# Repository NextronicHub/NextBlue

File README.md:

# Nextronic NextBlue

With nextBlue, your Iot and Bluetooth applications are  easier to make
it's a 5v 16Mhz board based on the ATmega328P microcontroller with a built-in Bluetooth connector
NextBlue can be programmed over a USB Mini-B cable using the Arduino IDE: Just plug in the board, select “Arduino UNO” from the board menu and you’re ready to upload code.
NextBlue has all of the hardware peripherals like the Arduino.

## Features

  ATmega328 microcontroller with Optiboot (UNO) Bootloader<br />
  Input voltage - 7-15V<br />
  0-5V outputs<br />
  14 Digital I/O Pins (6 PWM outputs)<br />
  6 Analog Inputs<br />
  I2C, UART and SPI<br />
  32k Flash Memory<br />
  16MHz Clock Speed<br />
  All SMD Construction<br />
  R3 Shield Compatible<br />
  Bluetooth connector (EN, 5V, GND, TX, RX, STATE) <br />
  Software/hardware serial selector switch for the Bluetooth<br />

<br />
<br />
[FTDI driver](http://www.ftdichip.com/Drivers/VCP.htm)

Nextronic Product page:[NextBlue](http://nextronic.ma/product/nextblue/).

you can by it at: [makershop.ma](http://makershop.ma/).

## Repository Contents

/Hardware - Design files (.brd, .sch)  
/Firmware - bootloader  
/Documentation - datasheet and examples

## Product Versions

NextBlue_V1 first release

## License Information

The hardware is released under [Creative Commons ShareAlike 4.0 International](https://creativecommons.org/licenses/by-sa/4.0/).

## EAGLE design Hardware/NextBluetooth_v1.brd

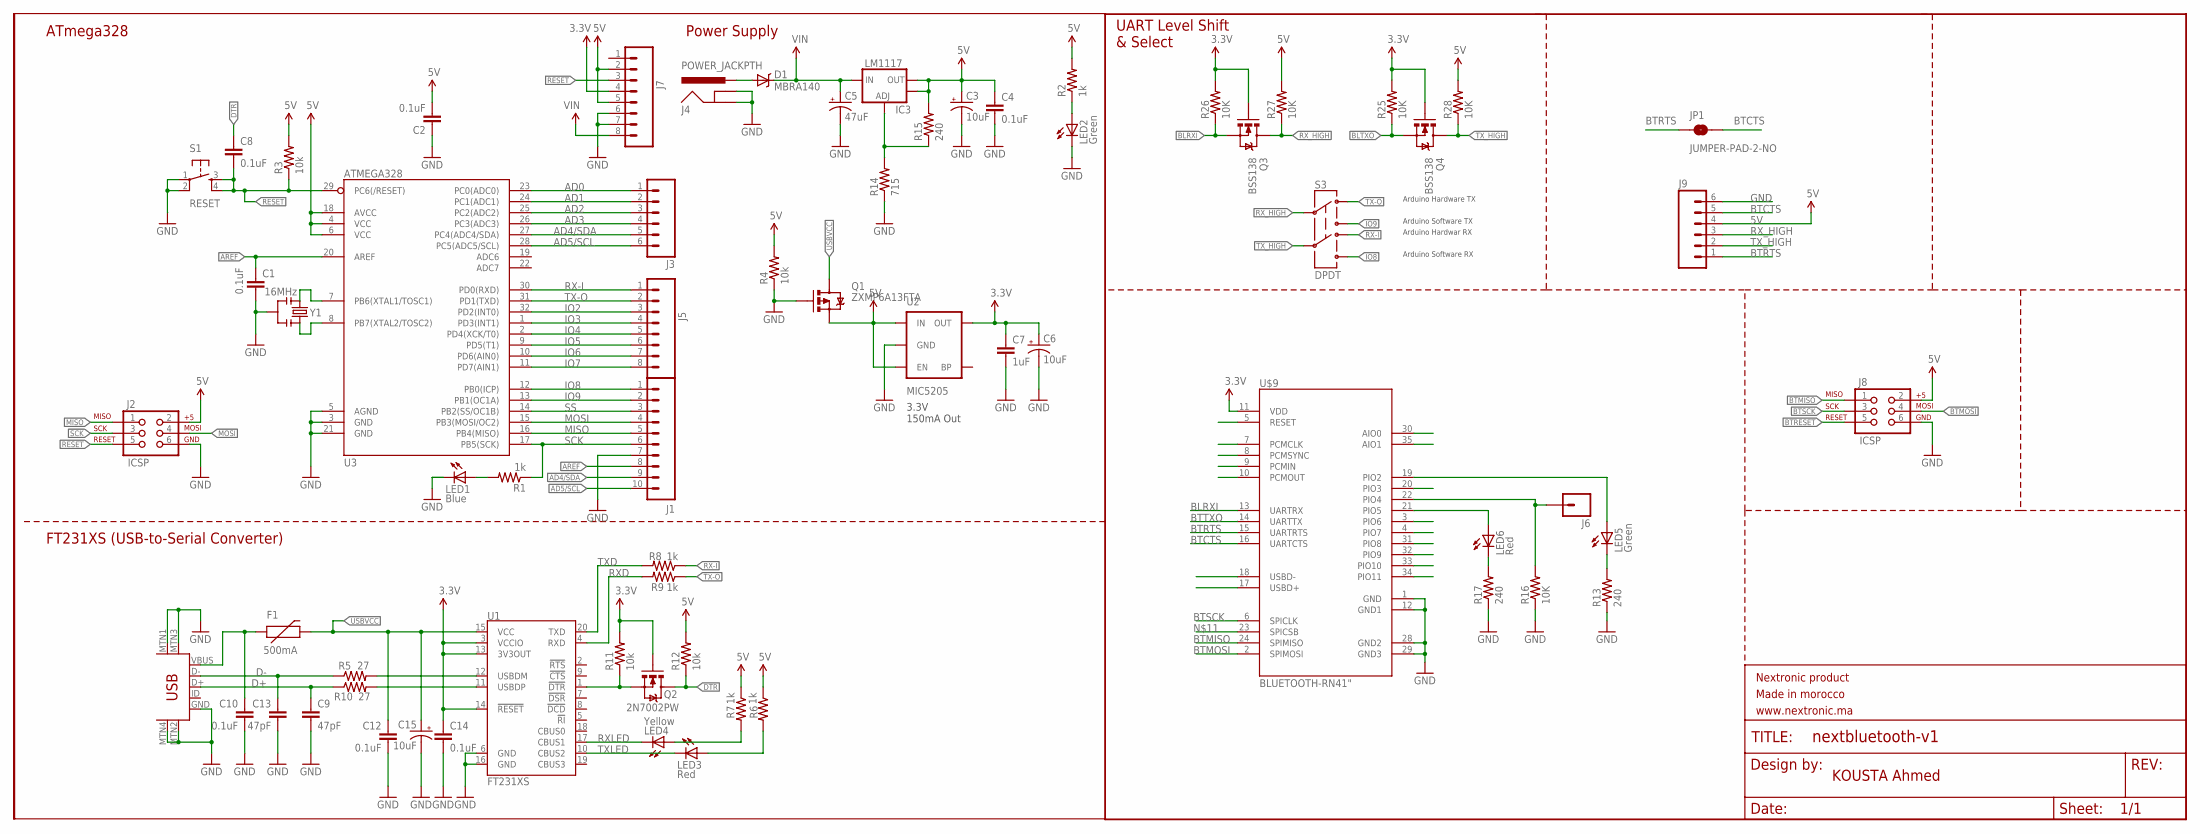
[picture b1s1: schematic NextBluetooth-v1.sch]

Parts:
C1, C2, C4, C8, C10, C12, C14: 0.1uF; 0603-CAP; MPN 0805B104K500CT
C3, C6, C15: 10uF; EIA3216; MPN MCSH21B104K101CT
C5: 47uF; PANASONIC_D; MPN EEEFT1H470AP
C7: 1uF; 0603-CAP; MPN ECA2GHG2R2
C9, C13: 47pF; 0603-CAP@1; MPN 08051A470JAT2A
D1: MBRA140; SMA-DIODE; MPN B140-13-F
F1: 500mA; PTC-1206; MPN 1N4148.
FRAME1: FRAME-LETTER; CREATIVE_COMMONS
IC3: LM1117; SOT223-ALT1; MPN LD1117S33TR
J1: M10SILK_FEMALE_PTH; 1X10
J2, J8: ICSP; 2X3
J3, J9: M06SILK_FEMALE_PTH; 1X06
J4: POWER_JACKPTH; POWER_JACK_PTH
J5, J7: M08; 1X08_ROUND
J6: M01NOSILK-KIT; 1X01NS-KIT
JP1: JUMPER-PAD-2-NO; PAD-JUMPER-2-NO_NO_SILK
LED1: Blue; LED-1206-NO_SILK; MPN 703-1028
LED2, LED5: Green; LED-1206-NO_SILK; MPN 703-1028
LED3, LED6: Red; LED-1206-NO_SILK; MPN 703-1028
LED4: Yellow; LED-1206-NO_SILK; MPN TLUY2401
Q1: ZXMP6A13FTA; SOT23-3; MPN ZXMP6A13FTA
Q2: 2N7002PW; SOT323; MPN 2N7002PW
Q3, Q4: BSS138; SOT23-3; MPN BSS138PW
R1, R2, R6, R7, R8, R9: 1k; 0603-RES; MPN ERA6AEB102V
R3, R4, R11, R12: 10k; 0603-RES; MPN MC0063W0603510K
R5, R10: 27; 0603-RES; MPN 22-27-2021
R13, R15, R17: 240; 0603-RES; MPN MCMR06X2200FTL
R14: 715; 0603-RES; MPN RC0603JR-07150RL
R16: 10K; 0603-RES; MPN RR0816P-103-B-T5
R25, R26, R27, R28: 10K; 0603-RES@2; MPN RR0816P-103-B-T5
S1: RESET; TACTILE_SWITCH_SMD
S3: DPDT; AYZ0202
U1: FT231XS; SSOP20_L; MPN FT231XS
U2: MIC5205; SOT23-5; MPN MIC5205-5.0YM5 TR
U3: ATMEGA328; TQFP32-08; MPN ATMEGA328P-AN
U$9: BLUETOOTH-RN41"; RN41
U$13: USB-MINIB-5PIN; USB-MINIB
Y1: 16MHz; RESONATOR-SMD

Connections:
3.3V: C6.A (+), C7.1, C14.1, J7.4, Q2.1 (G), Q3.1 (G), Q4.1 (G), R11.2, R25.2, R26.2, U1.3 (VCCIO), U1.13 (3V3OUT), U1.14 (!RESET), U2.5 (OUT), U$9.11 (VDD)
5V: C2.2, C3.A (+), C4.1, IC3.2 (OUT), IC3.4 (OUT), J2.2, J7.2, J7.5, J8.2, J9.4, Q1.2 (S), R2.2, R3.2, R4.2, R6.1, R7.1, R12.2, R15.2, R27.2, R28.2, U2.1 (IN), U2.3 (EN), U3.4 (VCC), U3.6 (VCC), U3.18 (AVCC)
AD0: J3.1, U3.23 (PC0(ADC0))
AD1: J3.2, U3.24 (PC1(ADC1))
AD2: J3.3, U3.25 (PC2(ADC2))
AD3: J3.4, U3.26 (PC3(ADC3))
AD4/SDA: J1.9, J3.5, U3.27 (PC4(ADC4/SDA))
AD5/SCL: J1.10, J3.6, U3.28 (PC5(ADC5/SCL))
AREF: C1.1, J1.8, U3.20 (AREF)
BLRXI: Q3.2 (S), R26.1, U$9.13 (UARTRX)
BLTXO: Q4.2 (S), R25.1
BTCTS: J9.5, JP1.2, U$9.16 (UARTCTS)
BTMISO: J8.1, U$9.24 (SPIMISO)
BTMOSI: J8.4, U$9.2 (SPIMOSI)
BTRESET: J8.5, U$9.5 (RESET)
BTRTS: J9.1, JP1.1, U$9.15 (UARTRTS)
BTSCK: J8.3, U$9.6 (SPICLK)
BTTXO: U$9.14 (UARTTX)
D+: C9.1, R10.1, U$13.D+
D-: C13.1, R5.1, U$13.D-
DTR: C8.1, Q2.3 (D), R12.1
GND: C1.2, C2.1, C3.C (-), C4.2, C5.-, C6.C (-), C7.2, C9.2, C10.2, C12.2, C13.2, C14.2, C15.C (-), J1.7, J2.6, J4.GND, J4.GNDBREAK, J7.6, J7.7, J8.6, J9.6, LED1.C, LED2.C, Q1.1 (G), R4.1, R13.1, R14.1, R16.1, R17.1, S1.1, S1.2, U1.6 (GND), U1.16 (GND), U2.2 (GND), U3.3 (GND), U3.5 (AGND), U3.21 (GND), U$9.1 (GND), U$9.12 (GND1), U$9.28 (GND2), U$9.29 (GND3), U$13.GND, U$13.MTN1 (MTN2), U$13.MTN2 (MTN3), U$13.MTN3 (MTN1), U$13.MTN4, Y1.2
IO2: J5.3, U3.32 (PD2(INT0))
IO3: J5.4, U3.1 (PD3(INT1))
IO4: J5.5, U3.2 (PD4(XCK/T0))
IO5: J5.6, U3.9 (PD5(T1))
IO6: J5.7, U3.10 (PD6(AIN0))
IO7: J5.8, U3.11 (PD7(AIN1))
IO8: J1.1, S3.6, U3.12 (PB0(ICP))
IO9: J1.2, S3.3, U3.13 (PB1(OC1A))
MISO: J1.5, J2.1, U3.16 (PB4(MISO))
MOSI: J1.4, J2.4, U3.15 (PB3(MOSI/OC2))
unnamed: LED1.A, R1.2
unnamed: LED2.A, R2.1
unnamed: U3.7 (PB6(XTAL1/TOSC1)), Y1.1
unnamed: U3.8 (PB7(XTAL2/TOSC2)), Y1.3
unnamed: D1.A, J4.PWR
unnamed: R5.2, U1.12 (USBDM)
unnamed: R10.2, U1.11 (USBDP)
unnamed: LED3.A, R6.2
unnamed: LED4.A, R7.2
unnamed: Q2.2 (S), R11.1, U1.1 (!DTR)
unnamed: IC3.1 (ADJ), R14.2, R15.1
unnamed: LED6.A, U$9.21 (PIO5)
unnamed: J6.1, R16.2, U$9.22 (PIO4)
unnamed: LED5.A, U$9.19 (PIO2)
unnamed: LED5.C, R13.2
unnamed: LED6.C, R17.2
RESET: C8.2, J2.5, J7.3, R3.1, S1.3, S1.4, U3.29 (PC6(/RESET))
RX-I: J5.1, R8.1, S3.4, U3.30 (PD0(RXD))
RXD: R9.2, U1.4 (RXD)
RXLED: LED4.C, U1.17 (CBUS1)
RX_HIGH: J9.3, Q3.3 (D), R27.1, S3.2
SCK: J1.6, J2.3, R1.1, U3.17 (PB5(SCK))
SS: J1.3, U3.14 (PB2(SS/OC1B))
TX-O: J5.2, R9.1, S3.1, U3.31 (PD1(TXD))
TXD: R8.2, U1.20 (TXD)
TXLED: LED3.C, U1.10 (CBUS2)
TX_HIGH: J9.2, Q4.3 (D), R28.1, S3.5
USBVCC: C12.1, C15.A (+), F1.2, Q1.3 (D), U1.15 (VCC)
VIN: C5.+, D1.C, IC3.3 (IN), J7.8
VUSB: C10.1, F1.1, U$13.VBUS

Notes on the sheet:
Power Supply
ATmega328
FT231XS (USB-to-Serial Converter)
3.3V 150mA Out
KOUSTA Ahmed
UART Level Shift & Select
Arduino Software TX
Arduino Software RX
Arduino Hardwar RX
Arduino Hardware TX

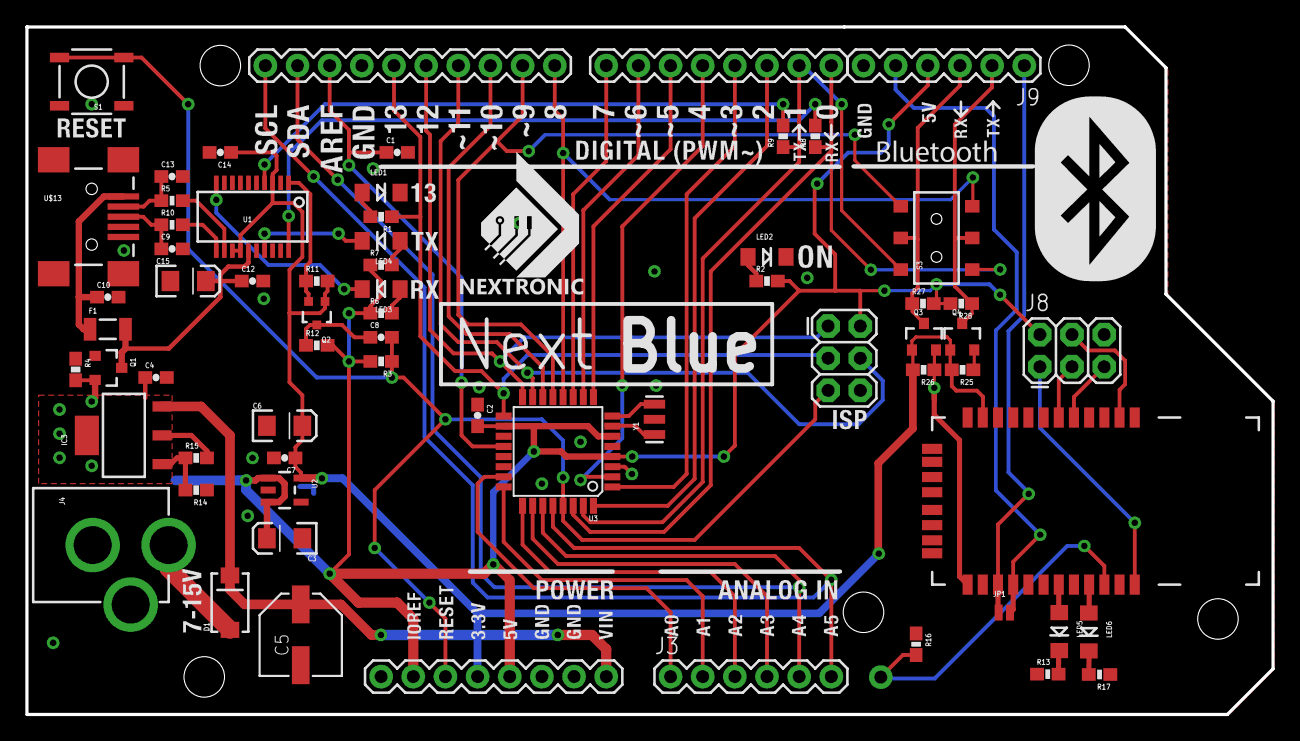
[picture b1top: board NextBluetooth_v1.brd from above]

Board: 2 copper layers, 98.4 x 54.3 mm, 67 parts (0 on the bottom side), 61 nets.

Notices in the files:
parts and their libraries:
SparkFun-Aesthetics: Licensing: CC v3.0 Share-Alike You are welcome to use this library for commercial purposes.
SparkFun-Electromechanical: Licensing: Creative Commons ShareAlike 4.0 International - https://creativecommons.org/licenses/by-sa/4.0
